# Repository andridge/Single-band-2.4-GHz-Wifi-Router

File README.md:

# Single-band-2.4-GHz-Wifi-Router
It combines advanced 802.11 b/g/n standards for efficient data transfer, a robust power output, expandable memory, and a flexible USB port for enhanced functionality.

Specifications
Medium-Speed Connectivity: Achieve reliable wireless speeds of 130Mbps in real-world scenarios through 802.11 b/g/n standards (Wi-Fi 4).
Signal Strength: Maintain a strong wireless signal with a power output of 20dBm or 100mW for extended coverage.
Memory and Processing Power: Facilitate firmware upgrades and manage concurrent connections by offering expandable flash memory (from 4MB to 16MB) and RAM (from 32MB to 64MB) preferable to accommodate the firmware as well as multiple device connectivity..
Versatile Connectivity: Provide a USB 2.0 port for High-Speed devices and accommodate Full/Low-Speed devices through an external High-Speed hub.
User-Friendly Power Management: Enable operation via a micro-USB socket for convenient and accessible power supply options.
Radio Bands: Single-band (2.4 GHz).
Limitations
Limited to 802.11n, which restricts its maximum speed to 150 Mbps, suitable for basic to moderate wireless needs.
Operates in a single band (2.4 GHz), potentially leading to more crowded frequencies and interference in environments with many wireless devices.
Lack of MU-MIMO support restricts simultaneous data transmission to only one device at a time, impacting overall network efficiency in dense or multi-device environments.
Lacks an antenna although it's integratable.

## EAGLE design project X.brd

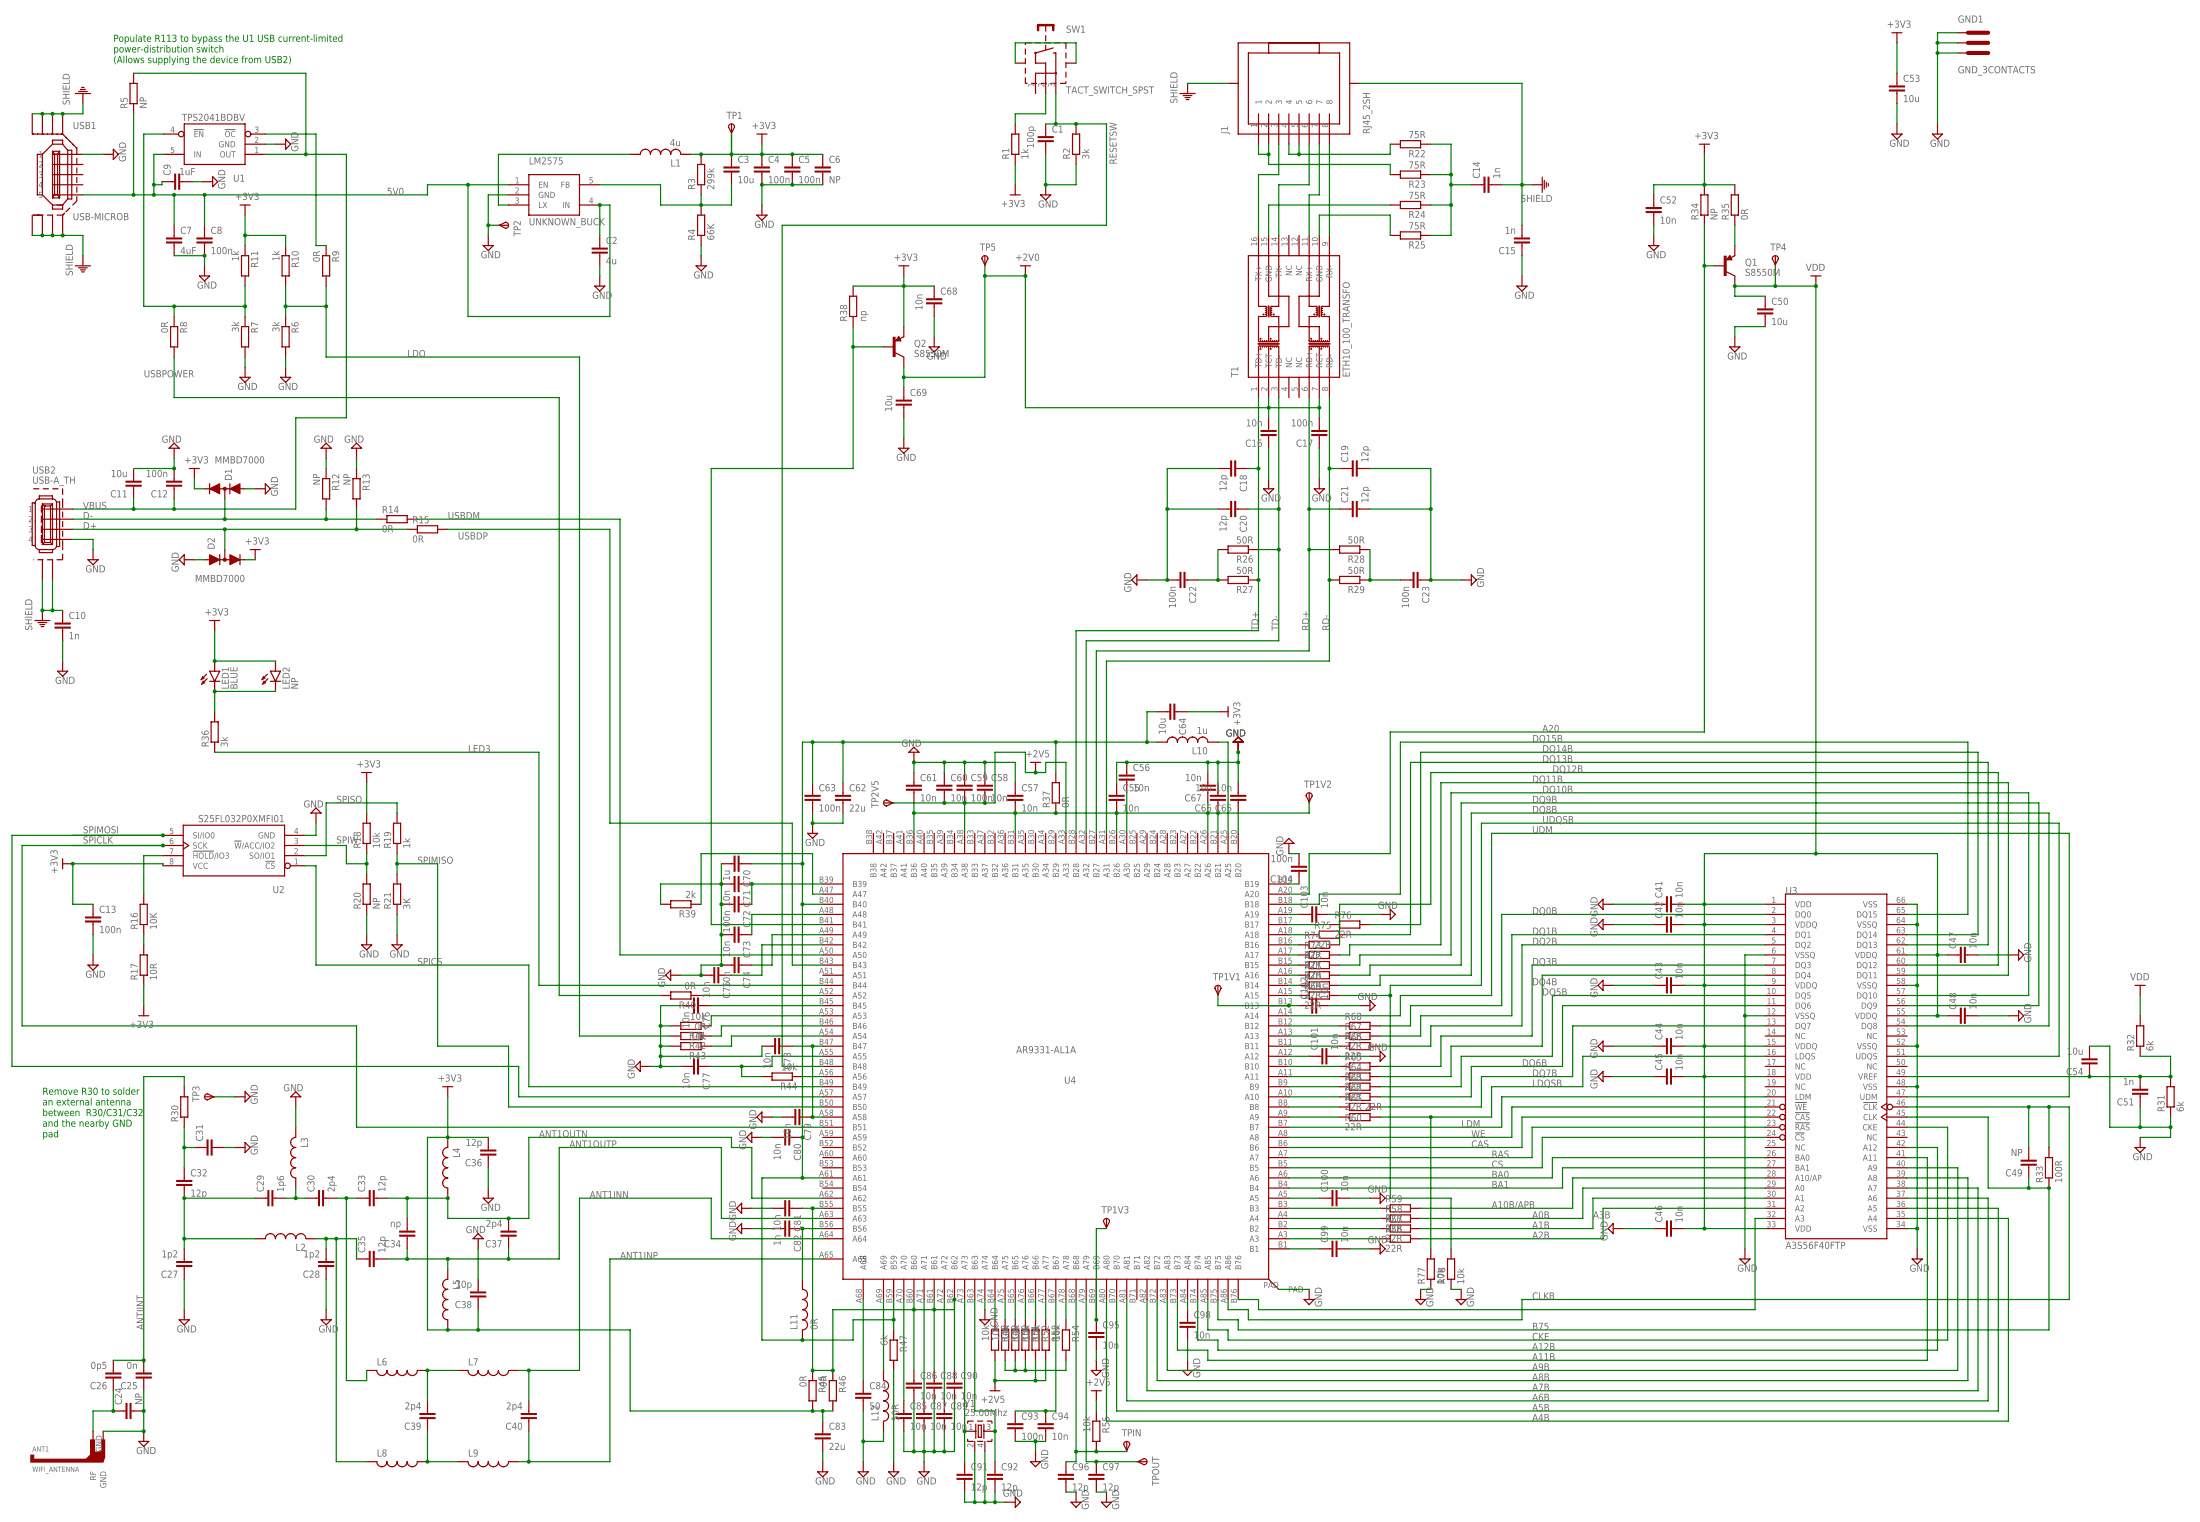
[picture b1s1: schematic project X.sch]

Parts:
ANT1: WIFI_ANTENNA
C1: 100p; C0402
C2: 4u; C0603
C3: 10u; C0603
C4, C5, C8, C13, C72, C93, C104: 100n; C0603
C6, C24, C49: NP; C0603
C7: 4uF; C0603
C9: 1uF; C0603
C10, C51, C82: 1n; C0603
C11, C50, C53, C54, C64: 10u; C0805
C12, C59, C63: 100n; C0805
C14, C15: 1n; C1206
C16: 10n; C1206
C17, C22, C23: 100n; C1206
C18, C19, C20, C21: 12p; C1206
C25: 0n; C0603
C26: 0p5; C0603
C27, C28: 1p2; C0603
C29: 1p6; C0603
C30, C37, C39, C40: 2p4; C0603
C31: CAP_0603; C0603
C32, C33, C35, C36, C91, C92, C96, C97: 12p; C0603
C34: np; C0603
C38: 10p; C0603
C41, C42, C43, C44, C45, C46, C47, C48, C52, C71, C73, C74, C75, C76, C77, C78, C79, C80, C81, C85, C86, C87, C88, C89, C90, C94, C95, C98, C99, C100, C101, C102, C103: 10n; C0603
C55, C56, C57, C58, C60, C61, C65, C66, C67: 10n; C0805
C62: 22u; C0805
C68: 10n; C0402
C69: 10u; C0402
C70: 1u; C0603
C83: 22u; C0603
C84: 50; C0603
D1, D2: MMBD7000; SOT23-3
GND1: GND_3CONTACTS; GND_3CONTACT
J1: RJ45_2SH; RJ45_LP_RA_SMT
L1: 4u; L0402
L2, L3, L4, L5, L6, L7, L8, L9: IND_0402; L0402
L10: 1u; L1008
L11: 0R; L0402
L12: 50R; L0402
LED1: BLUE; LED3MM
LED2: NP; LED3MM
LM2575: UNKNOWN_BUCK; SOT23-5
Q1, Q2: S8550M; SOT23-3
R1: 1k; R0402
R2: 3k; R0402
R3: 299k; R0603
R4: 66K; R0603
R5, R12, R13, R20, R34: NP; R0603
R6, R7, R36: 3k; R0603
R8, R9, R14, R15, R35, R37, R40, R42, R45, R46: 0R; R0603
R10, R11, R19: 1k; R0603
R16: 10K; R0603
R17: 10R; R0603
R18, R41, R43, R44, R48, R49, R50, R51, R52, R53, R54, R55, R77, R78: 10k; R0603
R21: 3K; R0603
R22, R23, R24, R25: 75R; R0402
R26, R27, R28, R29: 50R; R0402
R30: RES_0603; R0603
R31, R32, R47: 6k; R0603
R33: 100R; R0603
R38: np; R0603
R39: 2k; R0603
R56, R57, R58, R59, R60, R61, R62, R63, R64, R65, R66, R67, R68, R69, R70, R71, R72, R73, R74, R75, R76: 22R; R0603
SW1: TACT_SWITCH_SPST; TACT_SWITCH_SPST_RA_SMT
T1: ETH10_100_TRANSFO; H1601CG
TP1, TP1V1, TP1V2, TP1V3, TP2, TP2V5, TP3, TP4, TP5: TEST_PAD
TPIN: TEST_PAD
TPOUT: TEST_PAD
U1: TPS2041BDBV; SOT23-5
U2: S25FL032P0XMFI01; SOP8
U3: A3S56F40FTP; TSOP66
U4: AR9331-AL1A; DRMLF164
USB1: USB-MICROB
USB2: USB-A_TH
Y1: 25.00Mhz; CRYSTAL_32_25

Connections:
5V0: C2.1, C7.1, C8.1, C9.1, LM2575.1 (EN), LM2575.4 (IN), R5.1, U1.5 (IN), USB1.VBUS (5)
+2V0: C16.2, C17.2, C69.1, Q2.3 (C), T1.2 (TCT), T1.7 (RCT), TP5.1
+2V5: C58.2, C59.2, C60.2, R48.2, R52.2, R53.2, R55.1, TP2V5.1, U4.A33, U4.A38
+3V3: C3.1, C4.1, C5.1, C6.1, C13.1, C36.2, C38.1, C52.1, C53.1, C64.1, C68.1, C83.1, D1.2 (C), D2.2 (C), L1.2, L4.2, L5.1, LED1.A, LED2.A, Q2.2 (E), R1.1, R3.2, R10.1, R11.1, R17.1, R18.2, R34.2, R35.2, R38.2, R45.2, R46.2, TP1.1, U2.8 (VCC)
A0B: R58.2, U3.29 (A0)
A1B: R57.2, U3.30 (A1)
A2B: R56.2, U3.31 (A2)
A3B: U3.32 (A3), U4.B76
A4B: U3.35 (A4), U4.A80
A5B: U3.36 (A5), U4.B70
A6B: U3.37 (A6), U4.A81
A7B: U3.38 (A7), U4.A82
A8B: U3.39 (A8), U4.B72
A9B: U3.40 (A9), U4.A83
A10B/APB: R59.2, U3.28 (A10/AP)
A11B: U3.41 (A11), U4.B73
A12B: U3.42 (A12), U4.B74
A20: Q1.1 (B), R34.1, U4.A20
ANT1INN: C40.2, L7.1, U4.A64
ANT1INP: C40.1, L9.1, U4.A65
ANT1OUTN: C33.2, C34.2, C37.2, L4.1, U4.A62
ANT1OUTP: C34.1, C35.2, C37.1, L5.2, U4.A63
ANTIINT: C25.2, C26.2, R30.2
B75: C49.1, R33.1, U3.45 (CLK), U4.B75
BA0: U3.26 (BA0), U4.A6
BA1: U3.27 (BA1), U4.B4
CAS: U3.22 (!CAS), U4.B6
CKE: U3.44 (CKE), U4.A85
CLKB: C49.2, R33.2, U3.46 (!CLK), U4.A86
CS: U3.24 (!CS), U4.B5
D+: D2.3 (M), R13.2, R15.1, USB2.3
D-: D1.3 (M), R12.2, R14.1, USB2.2
DQ0B: R68.2, U3.2 (DQ0)
DQ1B: R67.2, U3.4 (DQ1)
DQ2B: R66.2, U3.5 (DQ2)
DQ3B: R65.2, U3.7 (DQ3)
DQ4B: R64.2, U3.8 (DQ4)
DQ5B: R63.2, U3.10 (DQ5)
DQ6B: R62.2, U3.11 (DQ6)
DQ7B: R61.2, U3.13 (DQ7)
DQ8B: R70.2, U3.54 (DQ8)
DQ9B: R71.2, U3.56 (DQ9)
DQ10B: R72.2, U3.57 (DQ10)
DQ11B: R73.2, U3.59 (DQ11)
DQ12B: R74.2, U3.60 (DQ12)
DQ13B: R75.2, U3.62 (DQ13)
DQ14B: R76.2, U3.63 (DQ14)
DQ15B: U3.65 (DQ15), U4.B18
GND: ANT1.GND, C1.2, C2.2, C4.2, C5.2, C6.2, C7.2, C8.2, C9.2, C10.2, C11.2, C12.2, C13.2, C15.1, C16.1, C17.1, C18.2, C19.2, C20.2, C21.2, C22.2, C23.1, C24.2, C25.1, C27.1, C28.1, C31.2, C36.1, C38.2, C41.1, C42.1, C43.1, C44.1, C45.1, C46.1, C47.2, C48.2, C50.2, C51.1, C52.2, C53.2, C54.2, C55.1, C56.1, C57.1, C58.1, C59.1, C60.1, C61.1, C62.2, C63.2, C65.2, C66.2, C67.2, C68.2, C69.2, C70.2, C71.2, C72.2, C73.2, C74.2, C75.2, C76.2, C77.2, C78.2, C79.2, C80.2, C81.2, C82.2, C83.2, C84.2, C85.2, C86.2, C87.2, C88.2, C89.2, C90.2, C91.2, C92.2, C93.2, C94.2, C95.2, C96.2, C97.2, C98.2, C99.2, C100.2, C101.2, C102.2, C103.2, C104.2, D1.1 (A), D2.1 (A), GND1.GND$1, GND1.GND$2, GND1.GND$3, L3.2, L12.2, LM2575.2 (GND), R2.1, R4.1, R6.2, R7.2, R12.1, R13.1, R20.1, R21.1, R31.1, R39.2, R41.2, R43.2, R47.2, R77.1, R78.1, TP2.1, TP3.1, U1.2 (GND), U2.4 (GND), U3.6 (VSSQ), U3.12 (VSSQ), U3.34 (VSS), U3.48 (VSS), U3.52 (VSSQ), U3.58 (VSSQ), U3.64 (VSSQ), U3.66 (VSS), U4.A74, U4.PAD, USB1.GND (1), USB2.4, Y1.2, Y1.4
LDM: U3.20 (LDM), U4.B7
LDO: R6.1, R9.2, R10.2, R42.2
LDQSB: R60.2, R77.2, U3.16 (LDQS)
LED3: R36.1, U4.B44
unnamed: C14.1, R22.1, R23.1, R24.1, R25.1
unnamed: R1.2, SW1.2
unnamed: SW1.S$1 (SH$1), SW1.S$2 (SH$2)
unnamed: C3.2, LM2575.5 (FB), R3.1, R4.2
unnamed: C71.1, C72.1, U4.B39
unnamed: Q2.1 (B), R38.1, U4.B41
unnamed: L1.1, LM2575.3 (LX)
unnamed: R7.1, R8.1, R11.2, U1.4 (!EN)
unnamed: C76.1, U4.B45
unnamed: R40.1, U4.A52
unnamed: R9.1, U1.3 (!OC)
unnamed: R16.1, R17.2
unnamed: R16.2, U2.7 (!HOLD!/IO3)
unnamed: J1.1, J1.2, R23.2
unnamed: J1.4, J1.5, R22.2
unnamed: J1.3, T1.16 (TX+)
unnamed: J1.6, T1.14 (TX-)
unnamed: R24.2, T1.15 (GND)
unnamed: J1.7, T1.11 (RX+)
unnamed: J1.8, T1.9 (RX-)
unnamed: R25.2, T1.10 (GND)
unnamed: R41.1, U4.A53
unnamed: R42.1, U4.B46
unnamed: C27.2, C29.1, C32.2, L2.1
unnamed: ANT1.RF, C24.1, C26.1
unnamed: C31.1, C32.1, R30.1
unnamed: C29.2, C30.1, L3.1
unnamed: C28.2, C35.1, L2.2, L8.2
unnamed: C22.1, R26.2, R27.2
unnamed: C30.2, C33.1, L6.2
unnamed: C23.2, R28.1, R29.1
unnamed: C51.2, C54.1, R31.2, R32.1, U3.49 (VREF)
unnamed: Q1.2 (E), R35.1
unnamed: C65.1, U4.B20
unnamed: C39.2, L6.1, L7.2
unnamed: C39.1, L8.1, L9.2
unnamed: R39.1, U4.A47
unnamed: LED1.K (C), LED2.K (C), R36.2
unnamed: C73.1, U4.A48
unnamed: C74.1, U4.A49
unnamed: C75.1, U4.B42
unnamed: C81.1, C86.1, C88.1, C90.1, R45.1, R46.1, U4.B55, U4.B60, U4.B61, U4.B62
unnamed: C56.2, U4.A30
unnamed: C55.2, C57.2, C61.2, C66.1, C67.1, R37.1, TP1V2.1, U4.A26, U4.B21, U4.B26, U4.B31, U4.B36
unnamed: C62.1, C63.1, C64.2, C70.1, C80.1, L10.1, L11.2, R37.2, R47.1, U4.A61, U4.B40, U4.B59
unnamed: R43.1, U4.A54
unnamed: C95.1, TP1V3.1, U4.B69
unnamed: C78.1, C79.1, U4.A58, U4.B47
unnamed: C82.1, L11.1, U4.B56
unnamed: C77.1, R44.2, U4.A55
unnamed: R44.1, U4.A56
unnamed: C91.1, U4.A73, Y1.1
unnamed: C84.1, U4.A68
unnamed: C92.1, U4.B63, Y1.3
unnamed: L12.1, U4.A69
unnamed: R49.2, R50.2, R51.2, R54.2
unnamed: C85.1, U4.A70
unnamed: R48.1, U4.B64
unnamed: C87.1, U4.A71
unnamed: R49.1, U4.A75
unnamed: C89.1, U4.A72
unnamed: R50.1, U4.B65
unnamed: R51.1, U4.A76
unnamed: R52.1, U4.B66
unnamed: R53.1, U4.A77
unnamed: R54.1, U4.A78
unnamed: C93.1, C94.1, U4.B67
unnamed: L10.2, U4.A25
unnamed: C96.1, R55.2, TPIN.1, U4.B68
unnamed: C97.1, TPOUT.1, U4.A79
unnamed: C98.1, U4.A84
unnamed: C99.1, U4.B1
unnamed: R56.1, U4.A3
unnamed: R57.1, U4.B2
unnamed: C100.1, U4.A5
unnamed: C101.1, U4.A12
unnamed: R66.1, U4.B11
unnamed: R61.1, U4.B8
unnamed: R62.1, U4.A10
unnamed: R63.1, U4.B9
unnamed: R64.1, U4.A11
unnamed: R65.1, U4.B10
unnamed: R59.1, U4.B3
unnamed: R58.1, U4.A4
unnamed: R60.1, U4.A9
unnamed: R67.1, U4.A13
unnamed: R68.1, U4.B12
unnamed: R69.1, U4.A15
unnamed: R70.1, U4.B14
unnamed: R71.1, U4.A16
unnamed: C102.1, TP1V1.1, U4.B13
unnamed: R73.1, U4.A17
unnamed: R72.1, U4.B15
unnamed: R74.1, U4.B16
unnamed: R75.1, U4.A18
unnamed: R76.1, U4.B17
unnamed: C103.1, U4.A19
unnamed: C104.1, U4.B19
RAS: U3.23 (!RAS), U4.A7
RD+: C21.1, R28.2, T1.6 (RD+), U4.B27
RD-: C19.1, R29.2, T1.8 (RD-), U4.A31
RESETSW: C1.1, R2.2, SW1.3, U4.B48
SHIELD: C10.1, C14.2, C15.2, J1.S$1 (SHIELD), J1.S$2 (SHIELD), USB1.P$1 (M0), USB1.P$2 (M7), USB1.S$1 (M1), USB1.S$2 (M2), USB1.S$3 (M3), USB1.S$4 (M4), USB1.S$5 (M5), USB1.S$6 (M6), USB2.S$1 (M1), USB2.S$2 (M2)
SPICLK: U2.6 (SCK), U4.B51
SPICS: U2.1 (!CS), U4.B49
SPIMISO: R19.1, R21.2, U4.B50
SPIMOSI: U2.5 (SI/IO0), U4.A57
SPISO: R19.2, U2.2 (SO/IO1)
SPIW: R18.1, R20.2, U2.3 (!W!/ACC/IO2)
TD+: C18.1, R27.1, T1.1 (TD+), U4.B28
TD-: C20.1, R26.1, T1.3 (TD-), U4.A32
UDM: U3.47 (UDM), U4.A14
UDQSB: R69.2, R78.2, U3.51 (UDQS)
USBDM: R14.2, U4.A50
USBDP: R15.2, U4.B43
USBPOWER: R8.2, R40.2
VBUS: C11.1, C12.1, R5.2, U1.1 (OUT), USB2.1
VDD: C41.2, C42.2, C43.2, C44.2, C45.2, C46.2, C47.1, C48.1, C50.1, Q1.3 (C), R32.2, TP4.1, U3.1 (VDD), U3.3 (VDDQ), U3.9 (VDDQ), U3.15 (VDDQ), U3.18 (VDD), U3.33 (VDD), U3.55 (VDDQ), U3.61 (VDDQ)
WE: U3.21 (!WE), U4.A8

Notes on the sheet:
Populate R113 to bypass the U1 USB current-limited power-distribution switch (Allows supplying the device from USB2)
Remove R30 to solder an external antenna between R30/C31/C32 and the nearby GND pad

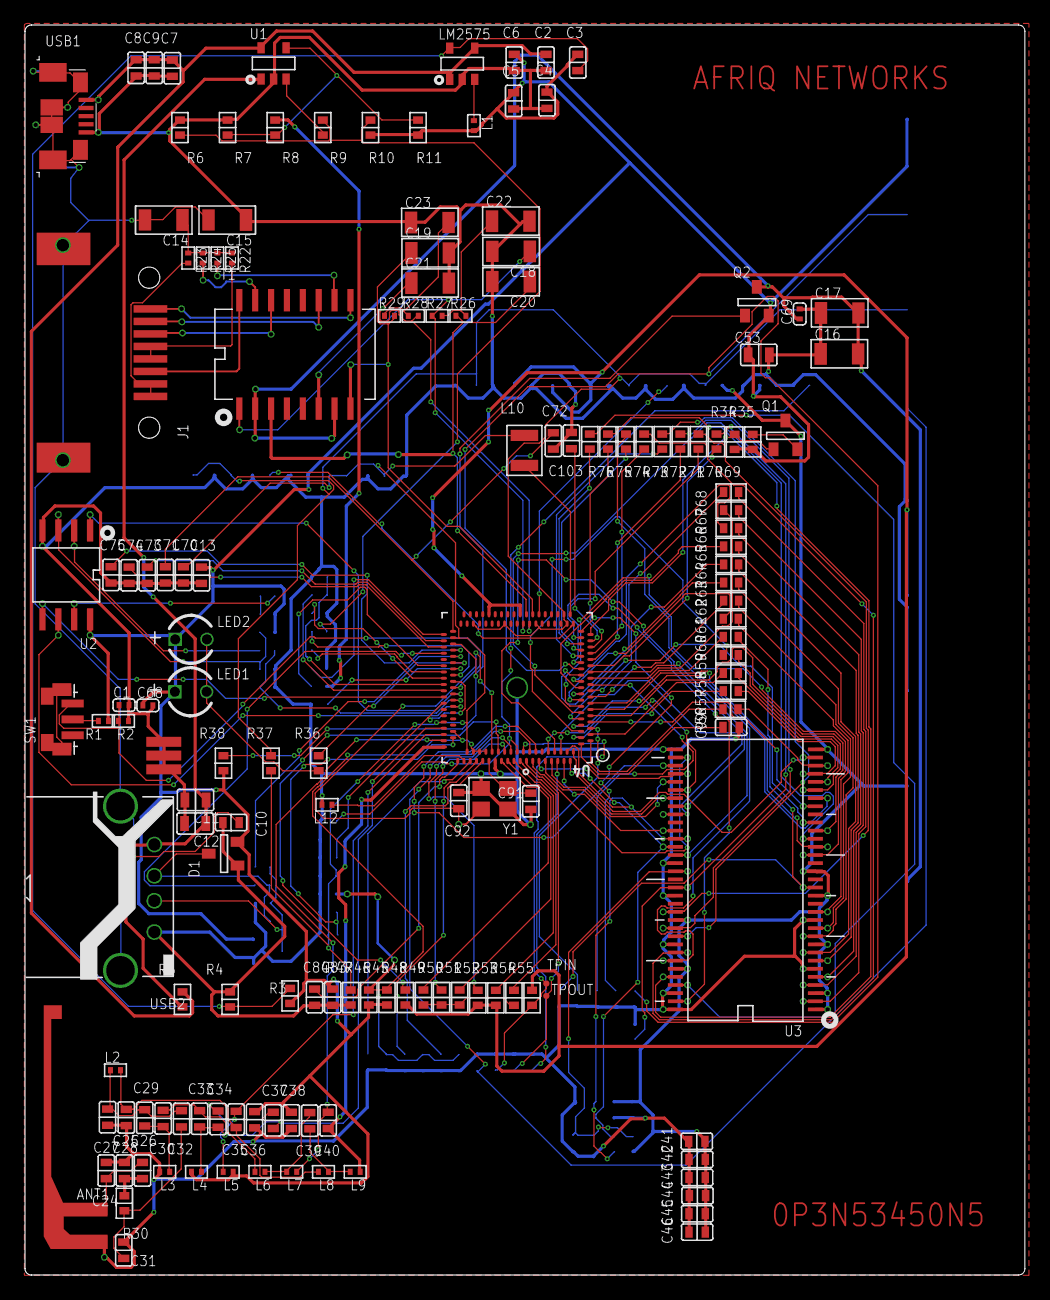
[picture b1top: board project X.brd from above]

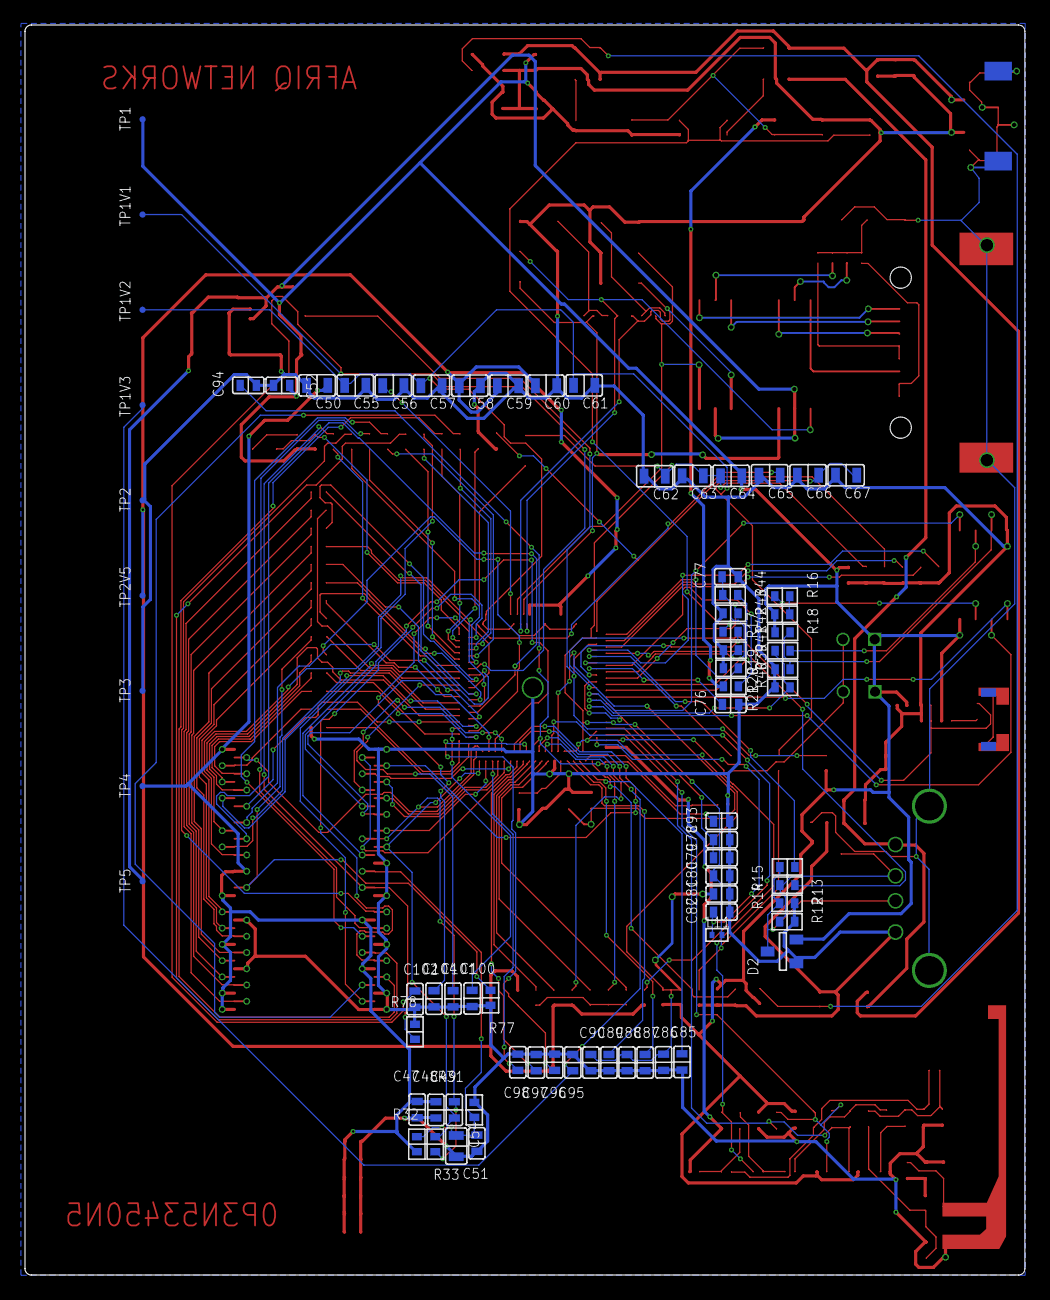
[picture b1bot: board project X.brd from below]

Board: 2 copper layers, 80.0 x 100.0 mm, 224 parts (75 on the bottom side), 172 nets.

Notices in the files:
parts and their libraries:
TL-WR703N: Copyright © 2012, Michel Stempin, All rights reserved
Licenced under Creative Commons CC BY-SA 3.0 license.
